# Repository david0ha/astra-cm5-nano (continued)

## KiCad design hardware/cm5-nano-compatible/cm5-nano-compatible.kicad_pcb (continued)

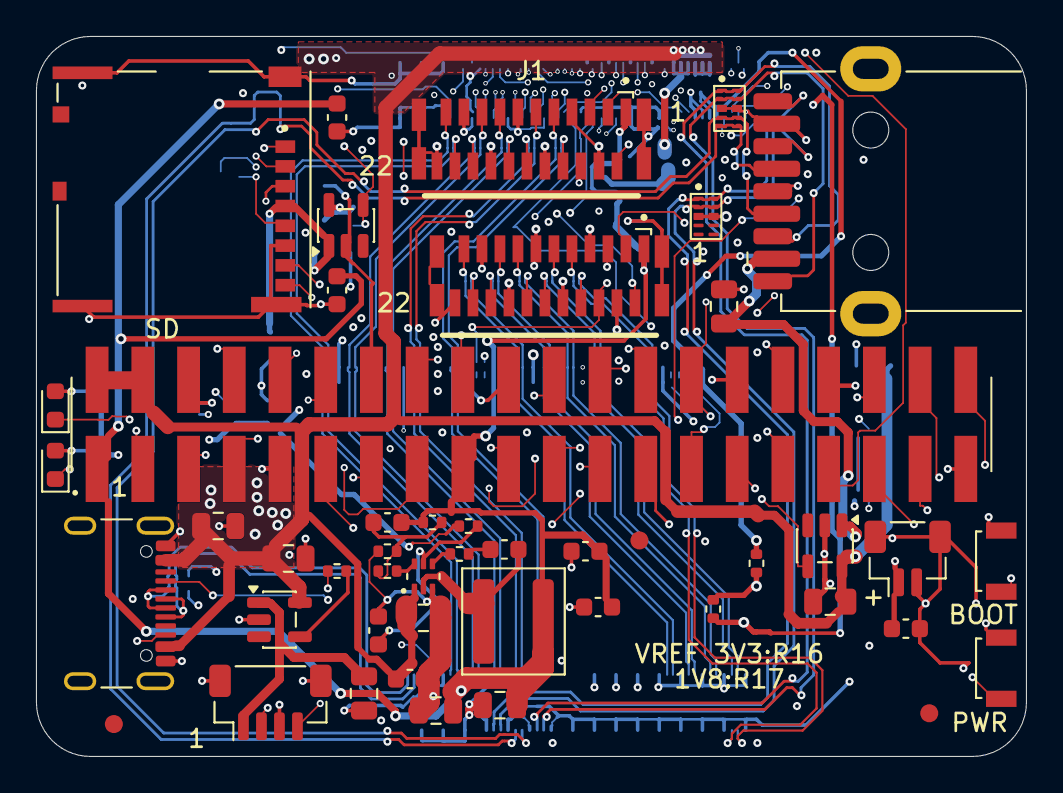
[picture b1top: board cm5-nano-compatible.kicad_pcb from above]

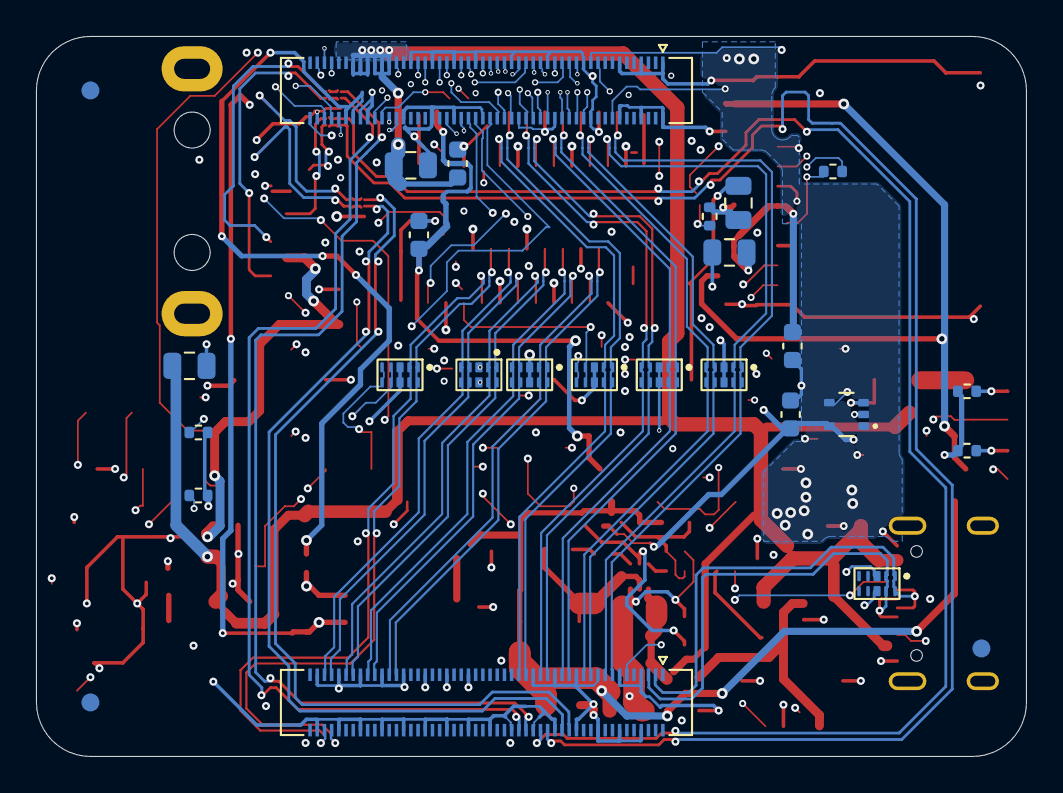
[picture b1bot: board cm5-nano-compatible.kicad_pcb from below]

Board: 8 copper layers, 55.0 x 40.0 mm, 74 parts (27 on the bottom side), 97 nets.

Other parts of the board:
FID1, FID2, FID3, FID4, FID5, FID6: Fiducial; Fiducial_1mm_Mask2mm

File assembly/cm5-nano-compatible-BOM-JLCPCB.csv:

Comment,Designator,Footprint,LCSC Part #
10uF GRM21BR61A106KE19L,"C1,C8,C9,C10,C11,C12,C23,C24,C26",C_0805_2012Metric,C77073
1uF GRM188R61A105KA61D,"C2,C14,C15,C19",C_0603_1608Metric,C86012
22uF CL21A226MQQNNNE,"C3,C6,C7",C_0805_2012Metric,C5674
100nF GRM188R71C104KA01D,"C4,C13,C16,C17,C18,C20,C25,C27",C_0603_1608Metric,C45000
15pF CL10C150JB8NNNC,C5,C_0603_1608Metric,C1644
10164227-1004A1RLF,"CM1,CM2",Amphenol_10164227_1004A1RLF,C7435219
1.8k RC0402FR-071K8L,"CM-R2,CM-R3",R_0402_1005Metric,C163481
Red LTST-C190KRKT,D1,LED_0603_1608Metric,C94869
Green LTST-C190KGKT,D2,LED_0603_1608Metric,C125094
BM02B-SRSS-TB(LF)(SN),H3,JST_SH_BM02B-SRSS-TB_1x02-1MP_P1.00mm_Vertical,C160388
BM04B-SRSS-TB(LF)(SN),H4,JST_SH_BM04B-SRSS-TB_1x04-1MP_P1.00mm_Vertical,C160390
FH12-22S-0.5SVA(54),"J1,J3",Hirose_FH12-22S-0.5SVA_22P_Vertical,C6250833
692122030100,J2,USB3_A_Receptacle_Wuerth_692122030100_silk,C5355286
B3U-3000P,"Key1,Key2",SW_SPST_B3U-3000P,C963349
3.3uH XAL5030-332MEC,L1,L_Coilcraft_XAL5030-XXX,C5342047
TSM-120-01-T-DV,PI1,Samtec_TSM-120-01-L-DV-P-TR_2x20_P2.54mm,C6723336
10 RC0402FR-0710RL,R2,R_0402_1005Metric,C138066
40.2k RC0402FR-0740K2L,R3,R_0402_1005Metric,C137983
10k RC0402FR-0710KL,"R5,R15",R_0402_1005Metric,C60490
75k RC0402FR-0775KL,R6,R_0402_1005Metric,C137935
0 RC0402JR-070RL,R7,R_0402_1005Metric,C60485
13k RC0402FR-0713KL,R9,R_0402_1005Metric,C138057
1k RC0402FR-071KL,"R10,R11",R_0402_1005Metric,C106235
22 RC0402FR-0722RL,R12,R_0402_1005Metric,C114765
0R RC0402FR-070RL,R16,R_0402_1005Metric,C106231
5033981892,TF1,SDCARD_MOLEX_503398-1892,C428492
USB4105-GF-A,Type_C1,USB_C_GCT_USB4105_GroundClearance_020,C3020560
MP1477GTF-Z,U1,MP1658_SOT563_MPS,C3193189
TPD4EUSB30DQAR,"U2,U5,U6,U7,U8,U10,U14,U16",TI_TPD4EUSB30_DQA0010A,C90627
RT9742CGJ5,U3,SOT-23-5,C250546
RT9742GGJ5,"U4,U11",SOT-23-5,C250547
TPD4EUSB30DQAR,U9,TI_TPD4EUSB30_DQA0010A_U9,C90627
74LVC1G07SE-7,U15,74LVC1G07_SOT353_Diodes,C67531
